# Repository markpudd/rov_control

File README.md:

Rov Control
===========

Ethernet/AVR/H-bridge board for ROV or general purpose control.  This is for an upcoming project.  

More details are available on [http://makicity.com/](http://makicity.com/)

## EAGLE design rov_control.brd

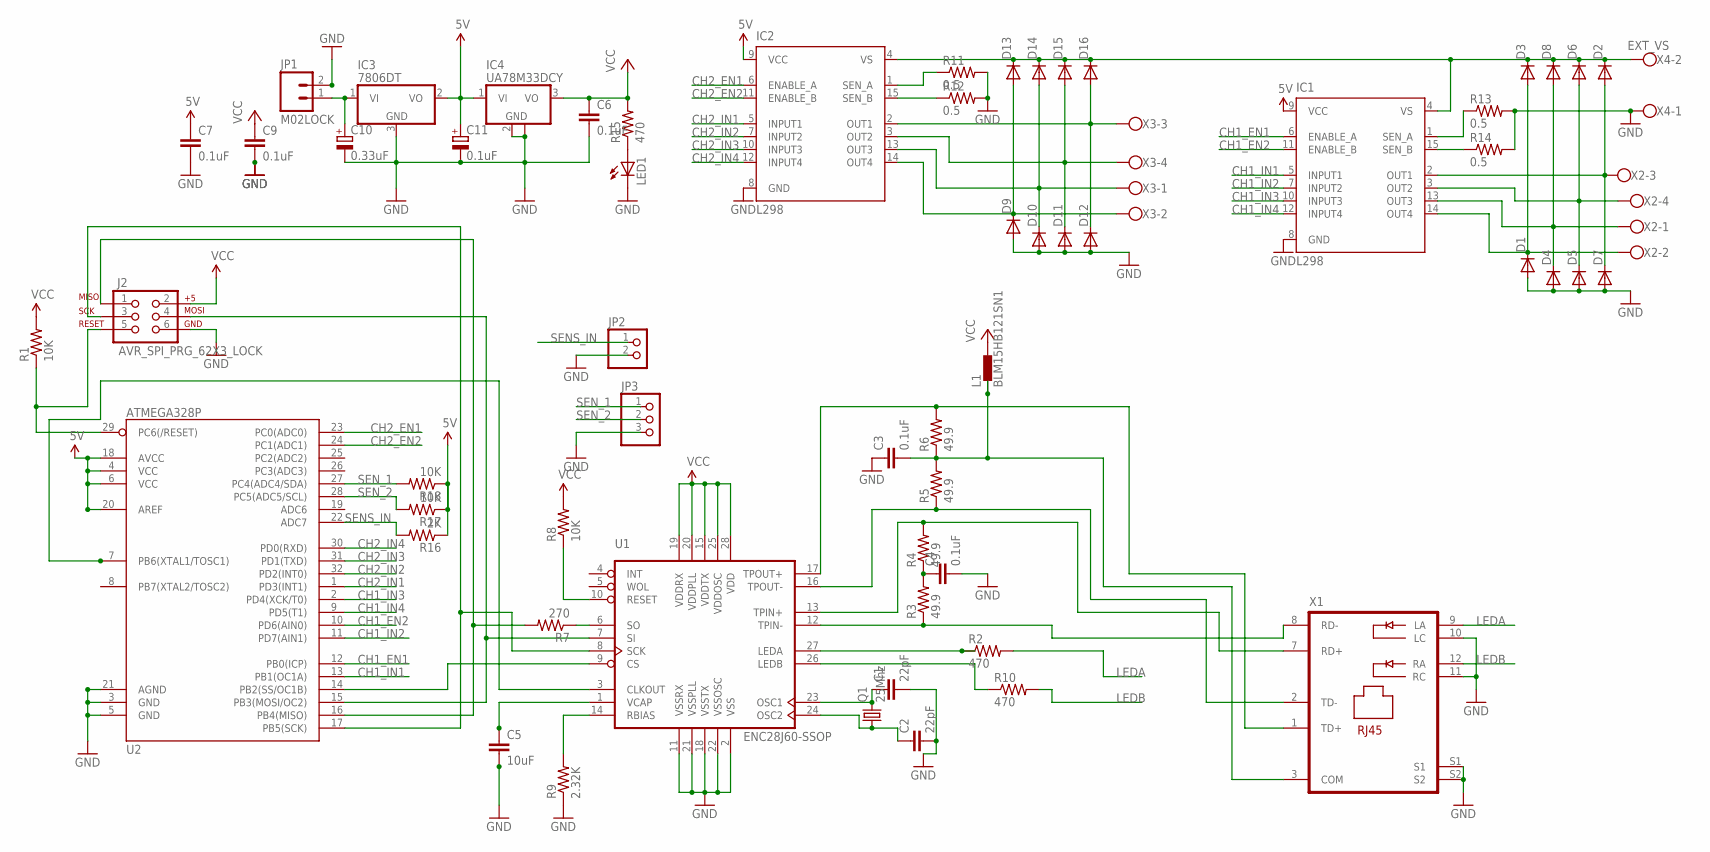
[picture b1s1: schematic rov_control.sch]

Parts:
C1, C2: 22pF; 0805
C3, C4, C6, C7, C9: 0.1uF; 0805
C5: 10uF; 0805
C10: 0.33uF; PANASONIC_A
C11: 0.1uF; PANASONIC_A
D1, D2, D3, D4, D5, D6, D7, D8, D9, D10, D11, D12, D13, D14, D15, D16: DIODESMA; SMA-DIODE
IC1, IC2: L298; MULTIWATT-15
IC3: 7806DT; TO252
IC4: UA78M33DCY; SOT223
J2: AVR_SPI_PRG_62X3_LOCK; 2X3_LOCK
JP1: M02LOCK; 1X02_LOCK
JP2: PINHD-1X2; 1X02
JP3: PINHD-1X3; 1X03
L1: BLM15HB121SN1; 0402
LED1: LEDSML0805; SML0805
Q1: 25Mhz; HC49UP
R1, R8, R17, R18: 10K; 0805
R2, R10, R15: 470; 0805
R3, R4, R5, R6: 49.9; 0805
R7: 270; 0805
R9: 2.32K; 0805
R11, R12, R13, R14: 0.5; 0805
R16: 2K; 0805
U1: ENC28J60-SSOP; SSOP28
U2: ATMEGA328P; TQFP32-08
X1: LU1T041X; PJ-J0
X2, X3: W237-4
X4: EXT_VS; W237-102

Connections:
5V: C7.1, C11.+, IC1.9 (VCC), IC2.9 (VCC), IC3.2 (VO), IC4.1 (VI), R16.1, R17.1, R18.1, U2.4 (VCC), U2.6 (VCC), U2.18 (AVCC), U2.20 (AREF)
CH1_EN1: IC1.6 (ENABLE_A), U2.12 (PB0(ICP))
CH1_EN2: IC1.11 (ENABLE_B), U2.10 (PD6(AIN0))
CH1_IN1: IC1.5 (INPUT1), U2.13 (PB1(OC1A))
CH1_IN2: IC1.7 (INPUT2), U2.11 (PD7(AIN1))
CH1_IN3: IC1.10 (INPUT3), U2.2 (PD4(XCK/T0))
CH1_IN4: IC1.12 (INPUT4), U2.9 (PD5(T1))
CH1_OUT1: D2.A, D7.C, IC1.2 (OUT1), X2.3
CH1_OUT2: D4.C, D8.A, IC1.13 (OUT3), X2.1
CH1_OUT3: D5.C, D6.A, IC1.3 (OUT2), X2.4
CH1_OUT4: D1.C, D3.A, IC1.14 (OUT4), X2.2
CH2_EN1: IC2.6 (ENABLE_A), U2.23 (PC0(ADC0))
CH2_EN2: IC2.11 (ENABLE_B), U2.24 (PC1(ADC1))
CH2_IN1: IC2.5 (INPUT1), U2.1 (PD3(INT1))
CH2_IN2: IC2.7 (INPUT2), U2.32 (PD2(INT0))
CH2_IN3: IC2.10 (INPUT3), U2.31 (PD1(TXD))
CH2_IN4: IC2.12 (INPUT4), U2.30 (PD0(RXD))
CH2_OUT1: D12.C, D16.A, IC2.2 (OUT1), X3.3
CH2_OUT2: D11.C, D15.A, IC2.3 (OUT2), X3.4
CH2_OUT3: D10.C, D14.A, IC2.13 (OUT3), X3.1
CH2_OUT4: D9.C, D13.A, IC2.14 (OUT4), X3.2
EXT_V: D2.C, D3.C, D6.C, D8.C, D13.C, D14.C, D15.C, D16.C, IC1.4 (VS), IC2.4 (VS), X4.2
GND: C1.2, C2.2, C3.1, C4.2, C5.2, C6.2, C7.2, C9.2, C10.-, C11.-, D1.A, D4.A, D5.A, D7.A, D9.A, D10.A, D11.A, D12.A, IC1.8 (GND), IC2.8 (GND), IC3.3 (GND), IC4.2 (GND), IC4.4 (GND), J2.6, JP1.2, JP2.2, JP3.3, LED1.C, R9.1, R11.2, R12.2, R13.2, R14.2, U1.2 (VSS), U1.11 (VSSRX), U1.18 (VSSTX), U1.21 (VSSPLL), U1.22 (VSSOSC), U2.3 (GND), U2.5 (GND), U2.21 (AGND), X1.10 (LC), X1.11 (RC), X1.S1, X1.S2, X4.1
LEDA: R2.2, X1.9 (LA)
LEDB: R10.2, X1.12 (RA)
unnamed: C2.1, Q1.1, U1.24 (OSC2)
unnamed: C1.1, Q1.2, U1.23 (OSC1)
unnamed: J2.3, U1.8 (SCK), U2.17 (PB5(SCK))
unnamed: J2.5, R1.1, U2.29 (PC6(/RESET))
unnamed: R2.1, U1.27 (LEDA)
unnamed: R10.1, U1.26 (LEDB)
unnamed: C4.1, R3.2, R4.1
unnamed: J2.1, R7.2, U2.16 (PB4(MISO))
unnamed: R7.1, U1.6 (SO)
unnamed: J2.4, U1.7 (SI), U2.15 (PB3(MOSI/OC2))
unnamed: U1.9 (CS), U2.14 (PB2(SS/OC1B))
unnamed: R8.1, U1.10 (RESET)
unnamed: LED1.A, R15.1
unnamed: R9.2, U1.14 (RBIAS)
unnamed: C5.1, U1.1 (VCAP)
unnamed: U1.3 (CLKOUT), U2.7 (PB6(XTAL1/TOSC1))
unnamed: C10.+, IC3.1 (VI), JP1.1
unnamed: IC2.1 (SEN_A), R11.1
unnamed: IC2.15 (SEN_B), R12.1
unnamed: IC1.1 (SEN_A), R13.1
unnamed: IC1.15 (SEN_B), R14.1
N-COM: R5.1, U1.16 (TPOUT-), X1.2 (TD-)
RD+: R4.2, U1.13 (TPIN+), X1.7 (RD+)
RD-: R3.1, U1.12 (TPIN-), X1.8 (RD-)
SENS_IN: JP2.1, R16.2, U2.22 (ADC7)
SEN_1: JP3.1, R18.2, U2.27 (PC4(ADC4/SDA))
SEN_2: JP3.2, R17.2, U2.28 (PC5(ADC5/SCL))
TD+: R6.2, U1.17 (TPOUT+), X1.1 (TD+)
TD-: C3.2, L1.1, R5.2, R6.1, X1.3 (COM)
VCC: C6.1, C9.1, IC4.3 (VO), J2.2, L1.2, R1.2, R8.2, R15.2, U1.15 (VDDTX), U1.19 (VDDRX), U1.20 (VDDPLL), U1.25 (VDDOSC), U1.28 (VDD)

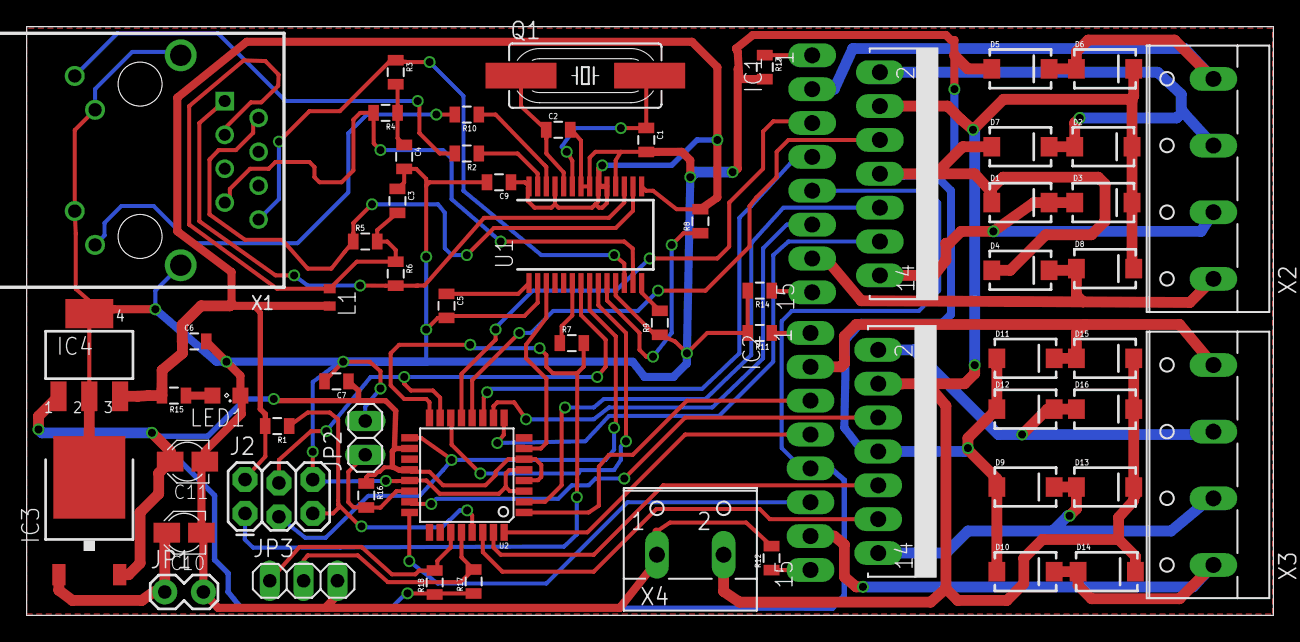
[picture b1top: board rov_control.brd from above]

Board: 2 copper layers, 93.5 x 44.2 mm, 61 parts (0 on the bottom side), 55 nets.

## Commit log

2014-08-11 Initial version

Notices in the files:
parts and their libraries:
SparkFun-Passives: Licensing: CC v3.0 Share-Alike You are welcome to use this library for commercial purposes.
